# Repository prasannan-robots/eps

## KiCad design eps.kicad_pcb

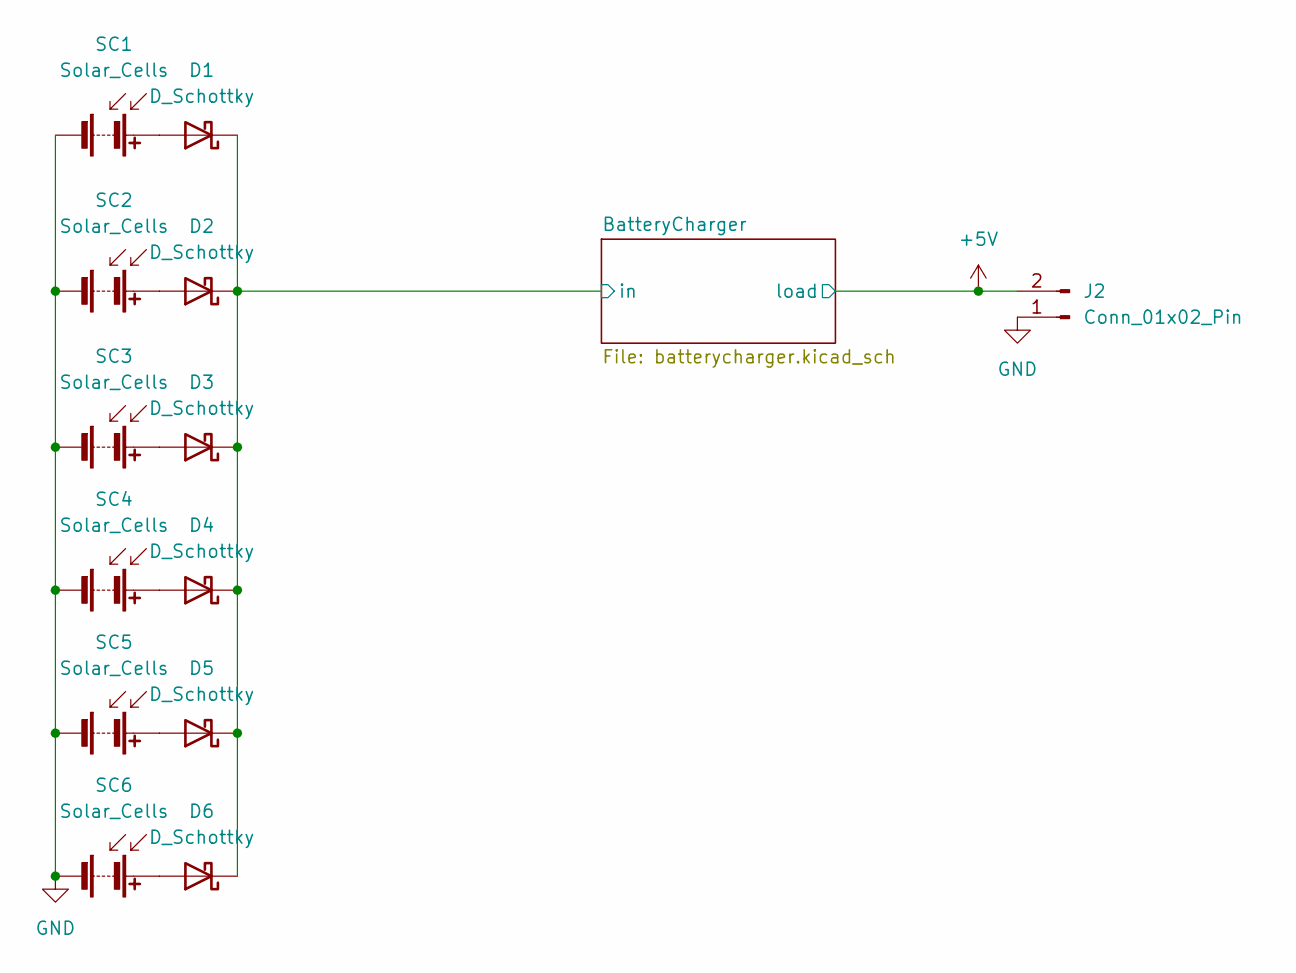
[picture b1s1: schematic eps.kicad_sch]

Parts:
D1, D2, D3, D4, D5, D6: D_Schottky; D_DO-35_SOD27_P7.62mm_Horizontal
J2: Conn_01x02_Pin; PinHeader_1x02_P2.54mm_Vertical
SC1, SC2, SC3, SC4, SC5, SC6: Solar_Cells; PinHeader_1x02_P2.54mm_Vertical

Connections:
+5V: J2.2; also elsewhere on the board
/BatteryCharger/in: D1.1 (K), D2.1 (K), D3.1 (K), D4.1 (K), D5.1 (K), D6.1 (K); also elsewhere on the board
GND: J2.1, SC1.2 (-), SC2.2 (-), SC3.2 (-), SC4.2 (-), SC5.2 (-), SC6.2 (-); also elsewhere on the board
unnamed: D1.2 (A), SC1.1 (+)
unnamed: D2.2 (A), SC2.1 (+)
unnamed: D3.2 (A), SC3.1 (+)
unnamed: D4.2 (A), SC4.1 (+)
unnamed: D5.2 (A), SC5.1 (+)
unnamed: D6.2 (A), SC6.1 (+)

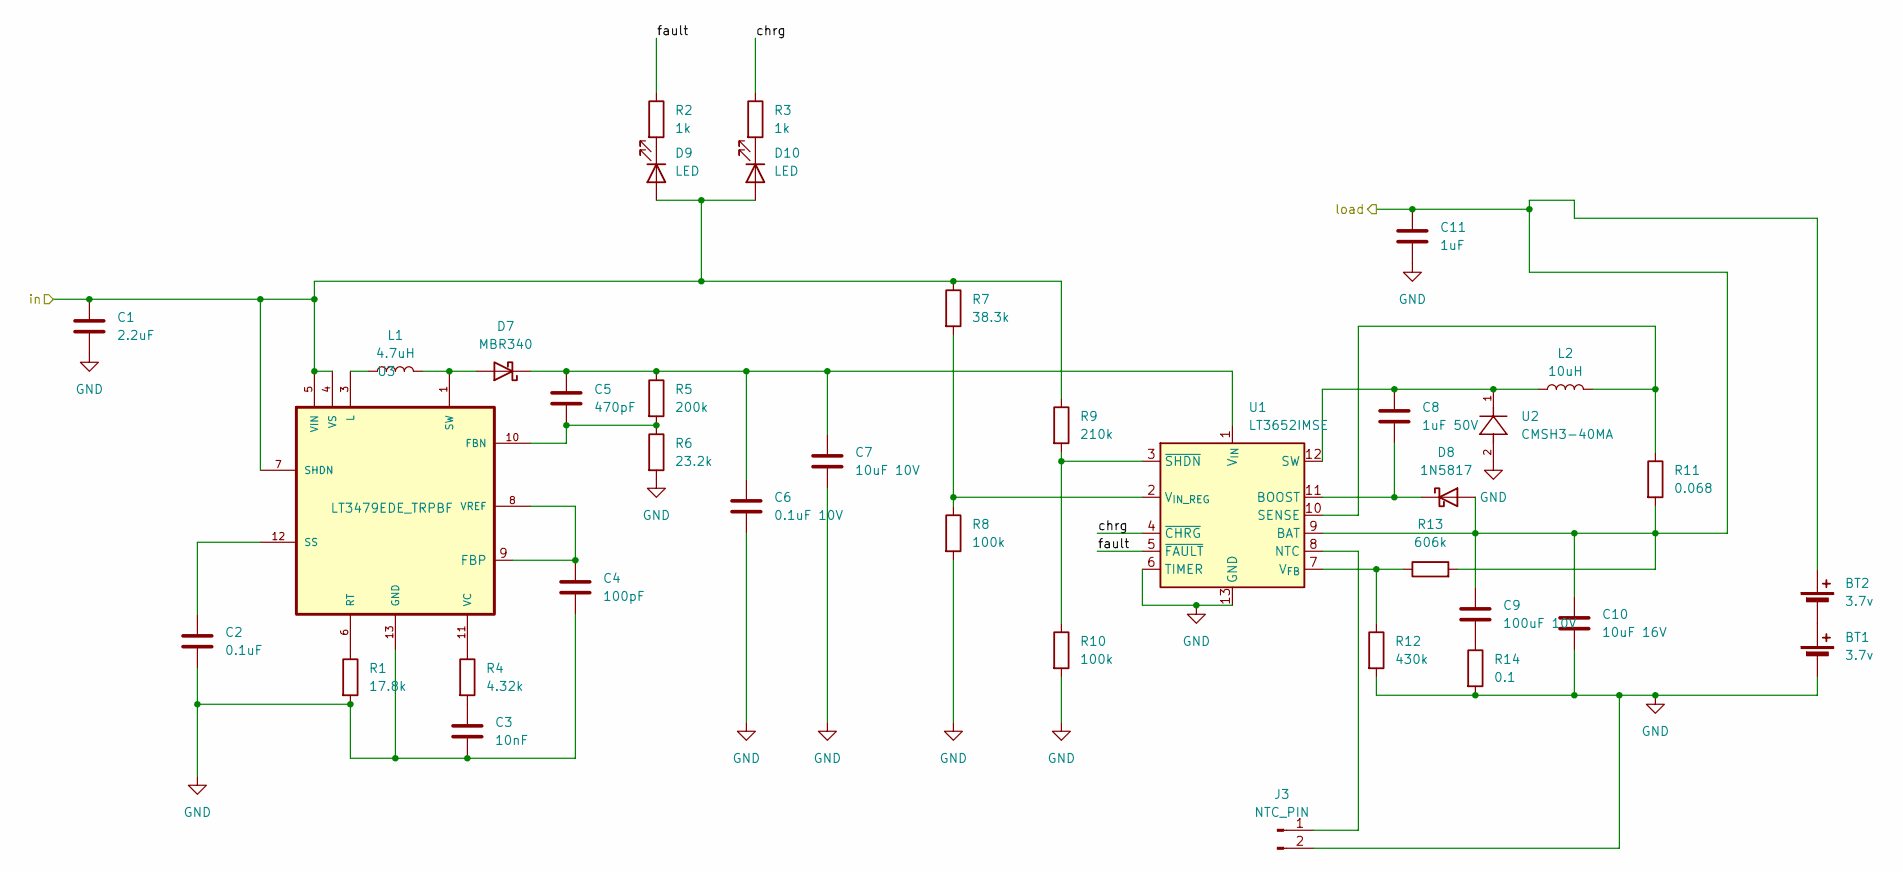
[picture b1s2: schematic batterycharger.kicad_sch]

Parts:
BT1, BT2: 3.7v; BatteryHolder_Keystone_1042_1x18650
C1: 2.2uF; C_0402_1005Metric_Pad0.74x0.62mm_HandSolder
C2: 0.1uF; C_0603_1608Metric_Pad1.08x0.95mm_HandSolder
C3: 10nF; C_0805_2012Metric_Pad1.18x1.45mm_HandSolder
C4: 100pF; C_0402_1005Metric_Pad0.74x0.62mm_HandSolder
C5: 470pF; C_0603_1608Metric_Pad1.08x0.95mm_HandSolder
C6: 0.1uF 10V; C_0201_0603Metric_Pad0.64x0.40mm_HandSolder
C7: 10uF 10V; C_0805_2012Metric_Pad1.18x1.45mm_HandSolder
C8: 1uF 50V; C_0402_1005Metric_Pad0.74x0.62mm_HandSolder
C9: 100uF 10V; C_Radial_D5.0mm_H11.0mm_P2.00mm
C10: 10uF 16V; C_0805_2012Metric_Pad1.18x1.45mm_HandSolder
C11: 1uF; C_0603_1608Metric_Pad1.08x0.95mm_HandSolder
D7: MBR340; D_DO-201AD_P15.24mm_Horizontal
D8: 1N5817; D_DO-41_SOD81_P10.16mm_Horizontal
D9, D10: LED; LED_D5.0mm
J3: NTC_PIN; PinHeader_1x02_P2.54mm_Vertical
L1: 4.7uH; L_Radial_D8.7mm_P5.00mm_Fastron_07HCP
L2: 10uH; L_2512_6332Metric_Pad1.52x3.35mm_HandSolder
R1: 17.8k; R_Axial_DIN0207_L6.3mm_D2.5mm_P15.24mm_Horizontal
R2, R3: 1k; R_Axial_DIN0207_L6.3mm_D2.5mm_P15.24mm_Horizontal
R4: 4.32k; R_Axial_DIN0207_L6.3mm_D2.5mm_P15.24mm_Horizontal
R5: 200k; R_Axial_DIN0207_L6.3mm_D2.5mm_P15.24mm_Horizontal
R6: 23.2k; R_Axial_DIN0207_L6.3mm_D2.5mm_P15.24mm_Horizontal
R7: 38.3k; R_Axial_DIN0207_L6.3mm_D2.5mm_P15.24mm_Horizontal
R8, R10: 100k; R_Axial_DIN0207_L6.3mm_D2.5mm_P15.24mm_Horizontal
R9: 210k; R_Axial_DIN0207_L6.3mm_D2.5mm_P15.24mm_Horizontal
R11: 0.068; R_Axial_DIN0207_L6.3mm_D2.5mm_P15.24mm_Horizontal
R12: 430k; R_Axial_DIN0207_L6.3mm_D2.5mm_P15.24mm_Horizontal
R13: 606k; R_Axial_DIN0207_L6.3mm_D2.5mm_P15.24mm_Horizontal
R14: 0.1; R_Axial_DIN0207_L6.3mm_D2.5mm_P15.24mm_Horizontal
U1: LT3652IMSE; MSOP-12-1EP_3x4mm_P0.65mm_EP1.65x2.85mm
U2: CMSH3-40MA; SMA
U3: LT3479EDE_TRPBF; DFN-14_DE_LIT

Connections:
+5V: BT2.1 (+), C9.1, C10.1, C11.1, D8.2 (A), R11.2, R13.2, U1.9 (BAT); also elsewhere on the board
/BatteryCharger/chrg: R3.1, U1.4 (~CHRG)
/BatteryCharger/fault: R2.1, U1.5 (~FAULT)
/BatteryCharger/in: C1.1, D9.2 (A), D10.2 (A), R7.1, R9.1, U3.4 (VS), U3.5 (VIN), U3.7 (SHDN); also elsewhere on the board
GND: BT1.2 (-), C1.2, C2.2, C3.2, C4.2, C6.2, C7.2, C10.2, C11.2, J3.2, R1.2, R6.2, R8.2, R10.2, R12.2, R14.2, U1.6 (TIMER), U1.13 (GND), U2.2, U3.13 (GND); also elsewhere on the board
unnamed: BT1.1 (+), BT2.2 (-)
unnamed: C3.1, R4.2
unnamed: C9.2, R14.1
unnamed: D7.2 (A), L1.2, U3.1 (SW)
unnamed: C5.1, C6.1, C7.1, D7.1 (K), R5.1, U1.1 (V_{IN})
unnamed: C8.2, D8.1 (K), U1.11 (BOOST)
unnamed: D9.1 (K), R2.2
unnamed: D10.1 (K), R3.2
unnamed: J3.1, U1.8 (NTC)
unnamed: L2.2, R11.1, U1.10 (SENSE)
unnamed: C8.1, L2.1, U1.12 (SW), U2.1
unnamed: R12.1, R13.1, U1.7 (V_{FB})
unnamed: R7.2, R8.1, U1.2 (V_{IN_REG})
unnamed: R9.2, R10.1, U1.3 (~SHDN)
unnamed: C5.2, R5.2, R6.1, U3.10 (FBN)
unnamed: C4.1, U3.8 (VREF), U3.9 (FBP)
unnamed: L1.1, U3.3 (L)
unnamed: R1.1, U3.6 (RT)
unnamed: C2.1, U3.12 (SS)
unnamed: R4.1, U3.11 (VC)

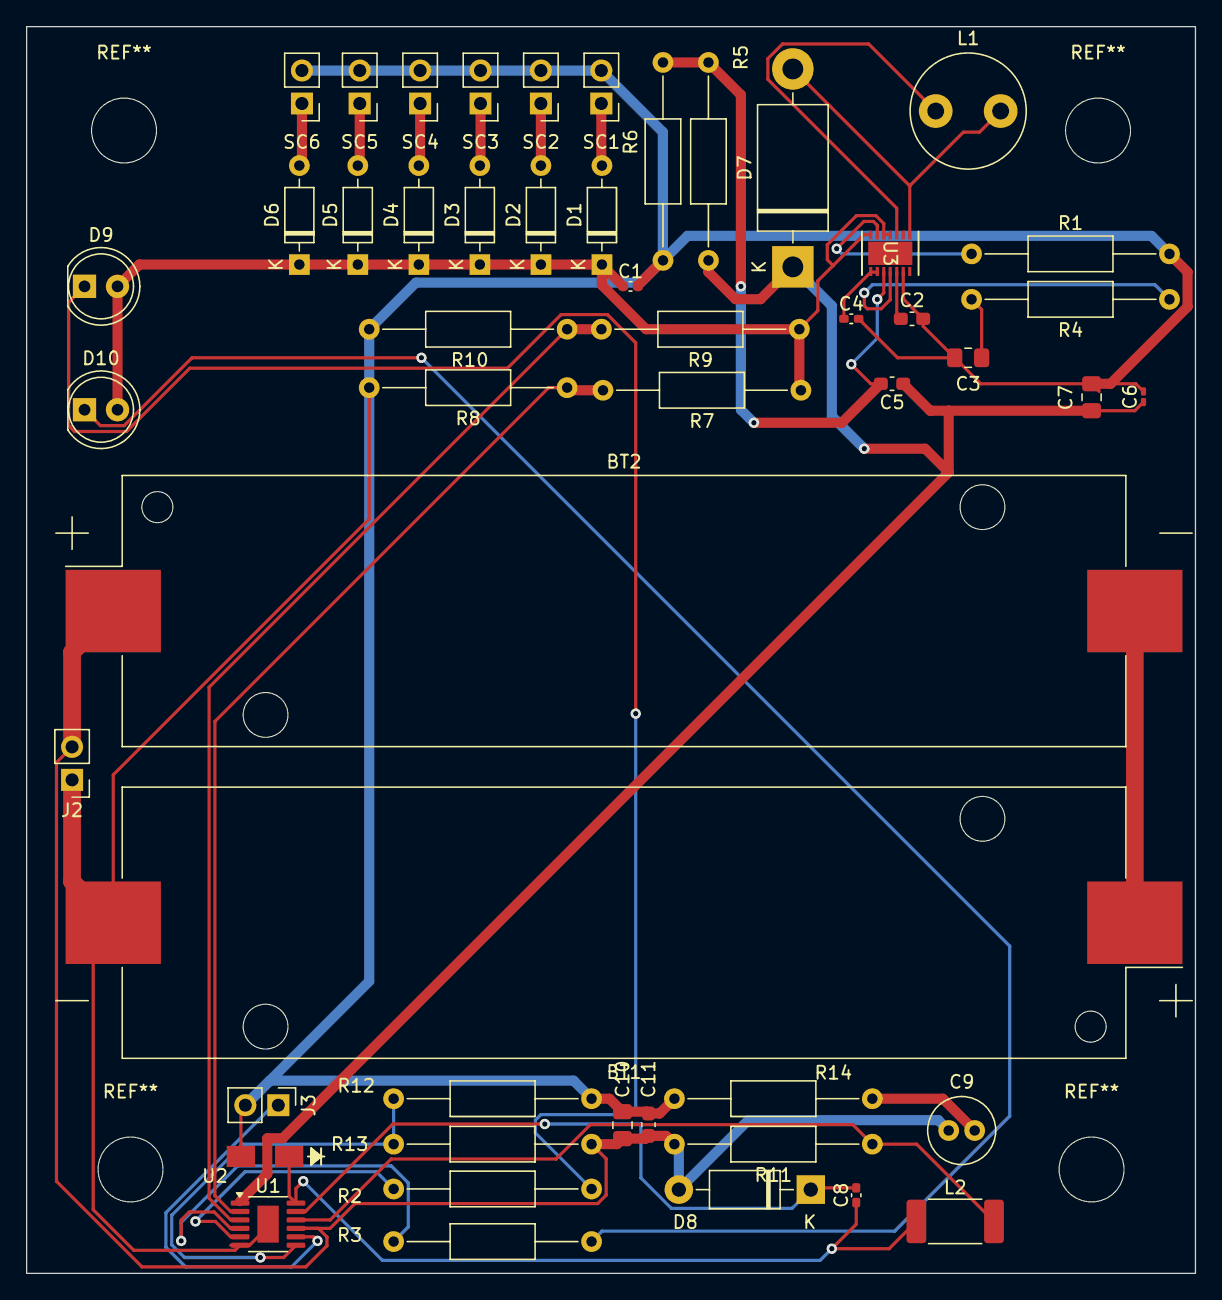
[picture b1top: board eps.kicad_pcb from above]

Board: 2 copper layers, 90.0 x 96.0 mm, 50 parts (0 on the bottom side), 31 nets.
